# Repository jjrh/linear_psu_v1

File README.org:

*Note: PCB renderings may be out of date!*

* about
- Simple linear powersupply using the LM78xx.

- version 1.1 fixes a footprint issue with the 78xx

* bom
** mouser shared project
   *note*: doesn't have the lm78xx, resistor leds, leds, or connectors included.
   http://www.mouser.com/ProjectManager/ProjectDetail.aspx?AccessID=abf0fe9c0d

#+START_IMAGES:

* images

	#+CAPTION:
	#+NAME:linear_psu_v1.sch.png
	#+attr_html: :width 800px
	[[./images/linear_psu_v1.sch.png]]

	#+CAPTION:
	#+NAME:linear_psu_v1-brd.png
	#+attr_html: :width 800px
	[[./images/linear_psu_v1-brd.png]]

	#+CAPTION:
	#+NAME:linear_psu_v1.png
	#+attr_html: :width 800px
	[[./images/linear_psu_v1.png]]

	#+CAPTION:
	#+NAME:linear_psu_v1_3d_2.png
	#+attr_html: :width 800px
	[[./images/linear_psu_v1_3d_2.png]]

	#+CAPTION:
	#+NAME:linear_psu_v1_3d_3.png
	#+attr_html: :width 800px
	[[./images/linear_psu_v1_3d_3.png]]

	#+CAPTION:
	#+NAME:linear_psu_v1_3d_1.png
	#+attr_html: :width 800px
	[[./images/linear_psu_v1_3d_1.png]]

* images/PCB

	#+CAPTION:
	#+NAME:copper_bottom.png.png
	#+attr_html: :width 800px
	[[./images/PCB/copper_bottom.png.png]]

	#+CAPTION:
	#+NAME:etch_mask_bottom.png.png
	#+attr_html: :width 800px
	[[./images/PCB/etch_mask_bottom.png.png]]

	#+CAPTION:
	#+NAME:silk_bottom.png.png
	#+attr_html: :width 800px
	[[./images/PCB/silk_bottom.png.png]]

	#+CAPTION:
	#+NAME:silk_top_mirror.png.png
	#+attr_html: :width 800px
	[[./images/PCB/silk_top_mirror.png.png]]

	#+CAPTION:
	#+NAME:copper_top_mirror.png.png
	#+attr_html: :width 800px
	[[./images/PCB/copper_top_mirror.png.png]]

	#+CAPTION:
	#+NAME:etch_mask_top_mirror.png.png
	#+attr_html: :width 800px
	[[./images/PCB/etch_mask_top_mirror.png.png]]

#+END_IMAGES:

* footnotes
  | Basic design | http://elinux.org/RPi_5V_PSU_construction |   |

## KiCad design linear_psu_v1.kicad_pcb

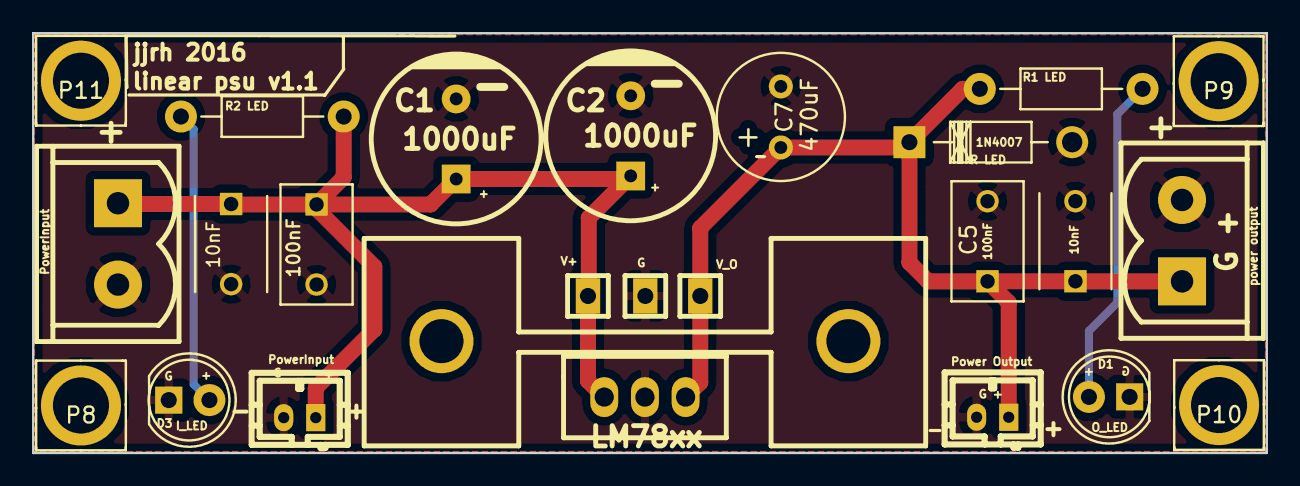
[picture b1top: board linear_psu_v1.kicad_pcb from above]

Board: 2 copper layers, 77.0 x 26.2 mm, 24 parts (0 on the bottom side), 5 nets.

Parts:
C1, C2: 1000uF; CP_10x30mm
C3, C6: 10nF; C_Disc_D6_P5
C4, C5: 100nF; C_Disc_D7.5_P5
C7: 470uF; Elko_vert_11.5x8mm_RM3.5
D1: O_LED; LED-5MM
D2: 1N4007; Diode_DO-41_SOD81_Horizontal_RM10
D3: I_LED; LED-5MM
P1: PowerInput; b2b-ph-kl
P2: PowerInput; mstbva_2,5%2f2-g-5,08
P3: GND_TESTPOINT; pin_socket_1
P4: V_IN_TESTPOINT; pin_socket_1
P5: G +; b2b-ph-kl
P6: G +; mstbva_2,5%2f2-g-5,08
P7: V_OUT_TESTPOINT; pin_socket_1
P8, P9, P10, P11: MOUNTING_HOLE; 3.5mm_m3
R1 LED, R2 LED: R; Resistor_Horizontal_RM10mm
U1: LM78xx; to220_std_14cw

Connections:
/REG_+5V: C5.1, C6.1, C7.1, D2.1, P5.1, P6.1, P7.1, R1 LED.1, U1.3
/V+: C1.1, C2.1, C3.1, C4.1, P1.1, P2.1, P4.1, R2 LED.1, U1.1
GNDPWR: C1.2, C2.2, C3.2, C4.2, C5.2, C6.2, C7.2, D1.1, D2.2, D3.1, P1.2, P2.2, P3.1, P5.2, P6.2, U1.2
unnamed: D1.2, R1 LED.2
unnamed: D3.2, R2 LED.2

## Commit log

2015-11-29 added files
2015-11-29 initialized readme
2015-11-29 forgot images
2015-11-29 generate more images
2015-11-29 updated readme, various changes to scripts
2015-11-29 updated readme, fixed generate readme to output correct paths
2015-11-29 test comment syntax
2015-11-29 okay this work
2015-11-29 updated README, generate readme script updated
2016-01-02 fixed bad footprint, rerouted board
2016-01-02 export files for production
2016-01-02 added images
2016-01-02 updated readme pictures
2016-01-02 added bom info
